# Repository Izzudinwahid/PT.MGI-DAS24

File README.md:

# PT.MGI-DAS24
Rangkaian Digital Alert System 24 Channel 110V

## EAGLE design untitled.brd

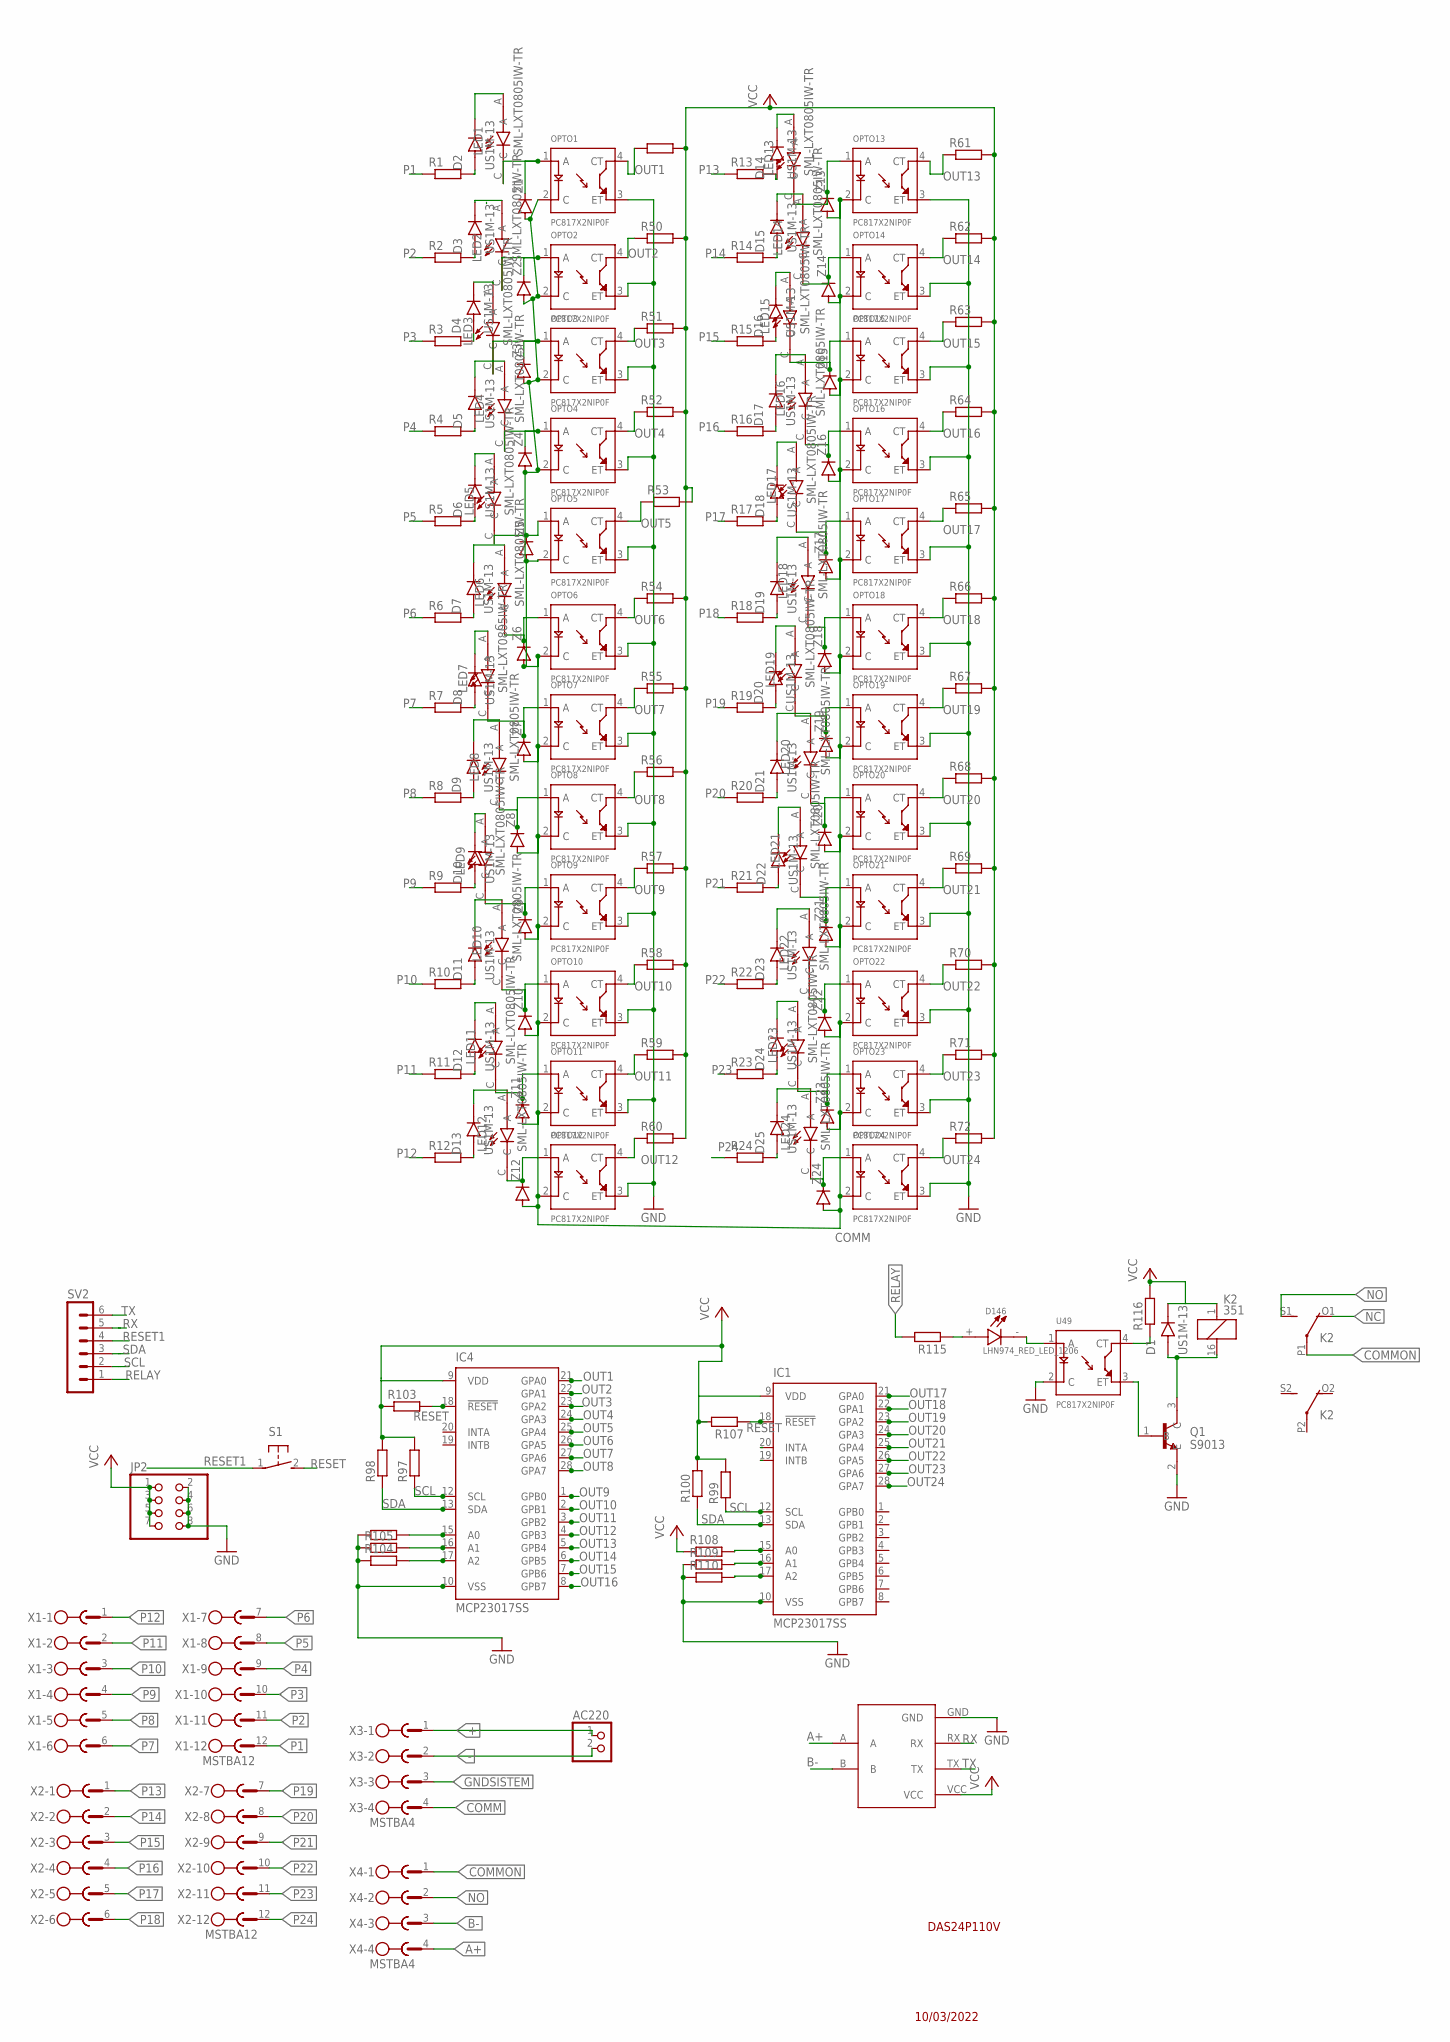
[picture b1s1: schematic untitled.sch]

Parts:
AC220: PINHD-1X2; 1X02
D1, D2, D3, D4, D5, D6, D7, D8, D9, D10, D11, D12, D13, D14, D15, D16, D17, D18, D19, D20, D21, D22, D23, D24, D25: US1M-13; DIOM5226X240N
D146: LHN974_RED_LED_1206; LEDC3216X120N
IC1, IC4: MCP23017SS; SSOP28DB
JP2: PINHD-2X4; 2X04
K2: 351
LED1, LED2, LED3, LED4, LED5, LED6, LED7, LED8, LED9, LED10, LED11, LED12, LED13, LED14, LED15, LED16, LED17, LED18, LED19, LED20, LED21, LED22, LED23, LED24: SML-LXT0805IW-TR; LEDC2012X120N
OPTO1, OPTO2, OPTO3, OPTO4, OPTO5, OPTO6, OPTO7, OPTO8, OPTO9, OPTO10, OPTO11, OPTO12, OPTO13, OPTO14, OPTO15, OPTO16, OPTO17, OPTO18, OPTO19, OPTO20, OPTO21, OPTO22, OPTO23, OPTO24: PC817X2NIP0F; SOT254P975X400-4N
Q1: S9013; SOT95P240X120-3N
R1, R2, R3, R4, R5, R6, R7, R8, R9, R10, R11, R12, R13, R14, R15, R16, R17, R18, R19, R20, R21, R22, R23, R24: R-EU_0414/15; 0414/15
R49, R50, R51, R52, R53, R54, R55, R56, R57, R58, R59, R60, R61, R62, R63, R64, R65, R66, R67, R68, R69, R70, R71, R72, R97, R98, R99, R100, R103, R104, R105, R106, R107, R108, R109, R110, R115, R116: R-EU_R0805; R0805
S1: 31-XX; B3F-31XX
SV2: MA06-1
TTL-RS1: TTL-RS485
U49: PC817X2NIP0F; SOT254P975X400-4N
X1, X2: MSTBA12
X3, X4: MSTBA4
Z1, Z2, Z3, Z4, Z5, Z6, Z7, Z8, Z9, Z10, Z11, Z12, Z13, Z14, Z15, Z16, Z17, Z18, Z19, Z20, Z21, Z22, Z23, Z24: DIODE-SOD123; SOD123

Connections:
+: AC220.1, X3.1; also elsewhere on the board
-: AC220.2, X3.2; also elsewhere on the board
A+: TTL-RS1.A, X4.4; also elsewhere on the board
B-: TTL-RS1.B, X4.3; also elsewhere on the board
COMM: OPTO1.2 (C), OPTO2.2 (C), OPTO3.2 (C), OPTO4.2 (C), OPTO5.2 (C), OPTO6.2 (C), OPTO7.2 (C), OPTO8.2 (C), OPTO9.2 (C), OPTO10.2 (C), OPTO11.2 (C), OPTO12.2 (C), OPTO13.2 (C), OPTO14.2 (C), OPTO15.2 (C), OPTO16.2 (C), OPTO17.2 (C), OPTO18.2 (C), OPTO19.2 (C), OPTO20.2 (C), OPTO21.2 (C), OPTO22.2 (C), OPTO23.2 (C), OPTO24.2 (C), X3.4, Z1.A, Z2.A, Z3.A, Z4.A, Z5.A, Z6.A, Z7.A, Z8.A, Z9.A, Z10.A, Z11.A, Z12.A, Z13.A, Z14.A, Z15.A, Z16.A, Z17.A, Z18.A, Z19.A, Z20.A, Z21.A, Z22.A, Z23.A, Z24.A; also elsewhere on the board
COMMON: K2.P1, X4.1; also elsewhere on the board
GND: IC1.10 (VSS), IC4.10 (VSS), JP2.2, JP2.4, JP2.6, JP2.8, OPTO1.3 (ET), OPTO2.3 (ET), OPTO3.3 (ET), OPTO4.3 (ET), OPTO5.3 (ET), OPTO6.3 (ET), OPTO7.3 (ET), OPTO8.3 (ET), OPTO9.3 (ET), OPTO10.3 (ET), OPTO11.3 (ET), OPTO12.3 (ET), OPTO13.3 (ET), OPTO14.3 (ET), OPTO15.3 (ET), OPTO16.3 (ET), OPTO17.3 (ET), OPTO18.3 (ET), OPTO19.3 (ET), OPTO20.3 (ET), OPTO21.3 (ET), OPTO22.3 (ET), OPTO23.3 (ET), OPTO24.3 (ET), Q1.2 (E), R104.1, R105.1, R106.1, R109.1, R110.1, TTL-RS1.GND, U49.2 (C)
unnamed: D2.A, R1.2
unnamed: LED10.C, OPTO10.1 (A), Z10.C
unnamed: D3.A, R2.2
unnamed: D4.A, R3.2
unnamed: LED1.C, OPTO1.1 (A), Z1.C
unnamed: D5.A, R4.2
unnamed: D2.C (K), LED1.A
unnamed: D6.A, R5.2
unnamed: D3.C (K), LED2.A
unnamed: D7.A, R6.2
unnamed: LED2.C, OPTO2.1 (A), Z2.C
unnamed: D8.A, R7.2
unnamed: D4.C (K), LED3.A
unnamed: D9.A, R8.2
unnamed: LED3.C, OPTO3.1 (A), Z3.C
unnamed: D15.A, R14.2
unnamed: D5.C (K), LED4.A
unnamed: LED4.C, OPTO4.1 (A), Z4.C
unnamed: D10.A, R9.2
unnamed: D6.C (K), LED5.A
unnamed: LED5.C, OPTO5.1 (A), Z5.C
unnamed: D7.C (K), LED6.A
unnamed: D11.A, R10.2
unnamed: D8.C (K), LED7.A
unnamed: LED6.C, OPTO6.1 (A), Z6.C
unnamed: D12.A, R11.2
unnamed: D13.A, R12.2
unnamed: D14.A, R13.2
unnamed: D16.A, R15.2
unnamed: D17.A, R16.2
unnamed: D9.C (K), LED8.A
unnamed: D10.C (K), LED9.A
unnamed: D11.C (K), LED10.A
unnamed: D18.A, R17.2
unnamed: D12.C (K), LED11.A
unnamed: D13.C (K), LED12.A
unnamed: D14.C (K), LED13.A
unnamed: D19.A, R18.2
unnamed: D15.C (K), LED14.A
unnamed: D16.C (K), LED15.A
unnamed: D17.C (K), LED16.A
unnamed: D20.A, R19.2
unnamed: D18.C (K), LED17.A
unnamed: D19.C (K), LED18.A
unnamed: D20.C (K), LED19.A
unnamed: D21.C (K), LED20.A
unnamed: D22.C (K), LED21.A
unnamed: D21.A, R20.2
unnamed: D23.C (K), LED22.A
unnamed: D24.C (K), LED23.A
unnamed: D25.C (K), LED24.A
unnamed: LED7.C, OPTO7.1 (A), Z7.C
unnamed: D22.A, R21.2
unnamed: LED8.C, OPTO8.1 (A), Z8.C
unnamed: LED9.C, OPTO9.1 (A), Z9.C
unnamed: LED11.C, OPTO11.1 (A), Z11.C
unnamed: LED12.C, OPTO12.1 (A), Z12.C
unnamed: D23.A, R22.2
unnamed: LED13.C, OPTO13.1 (A), Z13.C
unnamed: LED14.C, OPTO14.1 (A), Z14.C
unnamed: LED15.C, OPTO15.1 (A), Z15.C
unnamed: D24.A, R23.2
unnamed: LED16.C, OPTO16.1 (A), Z16.C
unnamed: LED17.C, OPTO17.1 (A), Z17.C
unnamed: LED18.C, OPTO18.1 (A), Z18.C
unnamed: D25.A, R24.2
unnamed: LED19.C, OPTO19.1 (A), Z19.C
unnamed: LED20.C, OPTO20.1 (A), Z20.C
unnamed: LED21.C, OPTO21.1 (A), Z21.C
unnamed: LED22.C, OPTO22.1 (A), Z22.C
unnamed: LED23.C, OPTO23.1 (A), Z23.C
unnamed: LED24.C, OPTO24.1 (A), Z24.C
unnamed: D146.-, U49.1 (A)
unnamed: D146.+, R115.1
unnamed: R116.1, U49.4 (CT)
unnamed: D1.A, K2.16 (2), Q1.3 (C)
unnamed: Q1.1 (B), U49.3 (ET)
unnamed: IC1.15 (A0), R108.2
unnamed: IC1.16 (A1), R109.2
unnamed: IC4.15 (A0), R106.2
unnamed: IC4.16 (A1), R105.2
unnamed: IC4.17 (A2), R104.2
unnamed: IC1.17 (A2), R110.2
NC: K2.O1 (O); also elsewhere on the board
NO: K2.S1 (S), X4.2; also elsewhere on the board
OUT1: IC4.21 (GPA0), OPTO1.4 (CT), R49.1
OUT2: IC4.22 (GPA1), OPTO2.4 (CT), R50.1
OUT3: IC4.23 (GPA2), OPTO3.4 (CT), R51.1
OUT4: IC4.24 (GPA3), OPTO4.4 (CT), R52.1
OUT5: IC4.25 (GPA4), OPTO5.4 (CT), R53.1
OUT6: IC4.26 (GPA5), OPTO6.4 (CT), R54.1
OUT7: IC4.27 (GPA6), OPTO7.4 (CT), R55.1
OUT8: IC4.28 (GPA7), OPTO8.4 (CT), R56.1
OUT9: IC4.1 (GPB0), OPTO9.4 (CT), R57.1
OUT10: IC4.2 (GPB1), OPTO10.4 (CT), R58.1
OUT11: IC4.3 (GPB2), OPTO11.4 (CT), R59.1
OUT12: IC4.4 (GPB3), OPTO12.4 (CT), R60.1
OUT13: IC4.5 (GPB4), OPTO13.4 (CT), R61.1
OUT14: IC4.6 (GPB5), OPTO14.4 (CT), R62.1
OUT15: IC4.7 (GPB6), OPTO15.4 (CT), R63.1
OUT16: IC4.8 (GPB7), OPTO16.4 (CT), R64.1
OUT17: IC1.21 (GPA0), OPTO17.4 (CT), R65.1
OUT18: IC1.22 (GPA1), OPTO18.4 (CT), R66.1
OUT19: IC1.23 (GPA2), OPTO19.4 (CT), R67.1
OUT20: IC1.24 (GPA3), OPTO20.4 (CT), R68.1
OUT21: IC1.25 (GPA4), OPTO21.4 (CT), R69.1
OUT22: IC1.26 (GPA5), OPTO22.4 (CT), R70.1
OUT23: IC1.27 (GPA6), OPTO23.4 (CT), R71.1
OUT24: IC1.28 (GPA7), OPTO24.4 (CT), R72.1
P1: R1.1, X1.12
P2: R2.1, X1.11
P3: R3.1, X1.10
P4: R4.1, X1.9
P5: R5.1, X1.8
P6: R6.1, X1.7
P7: R7.1, X1.6
P8: R8.1, X1.5
P9: R9.1, X1.4
P10: R10.1, X1.3
P11: R11.1, X1.2
P12: R12.1, X1.1
P13: R13.1, X2.1
P14: R14.1, X2.2
P15: R15.1, X2.3
P16: R16.1, X2.4
P17: R17.1, X2.5
P18: R18.1, X2.6
P19: R19.1, X2.7
P20: R20.1, X2.8
P21: R21.1, X2.9
P22: R22.1, X2.10
P23: R23.1, X2.11
P24: R24.1, X2.12
RELAY: R115.2, SV2.1
RESET: IC1.18 (!RESET), IC4.18 (!RESET), R103.2, R107.1, S1.2 (S)
RESET1: S1.1, SV2.4
RX: SV2.5, TTL-RS1.RX
SCL: IC1.12 (SCL), IC4.12 (SCL), R97.1, R99.1, SV2.2
SDA: IC1.13 (SDA), IC4.13 (SDA), R98.1, R100.1, SV2.3
TX: SV2.6, TTL-RS1.TX
VCC: D1.C (K), IC1.9 (VDD), IC4.9 (VDD), JP2.1, JP2.3, JP2.5, JP2.7, K2.1, R49.2, R50.2, R51.2, R52.2, R53.2, R54.2, R55.2, R56.2, R57.2, R58.2, R59.2, R60.2, R61.2, R62.2, R63.2, R64.2, R65.2, R66.2, R67.2, R68.2, R69.2, R70.2, R71.2, R72.2, R97.2, R98.2, R99.2, R100.2, R103.1, R107.2, R108.1, R116.2, TTL-RS1.VCC

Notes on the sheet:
DAS24P110V
10/03/2022

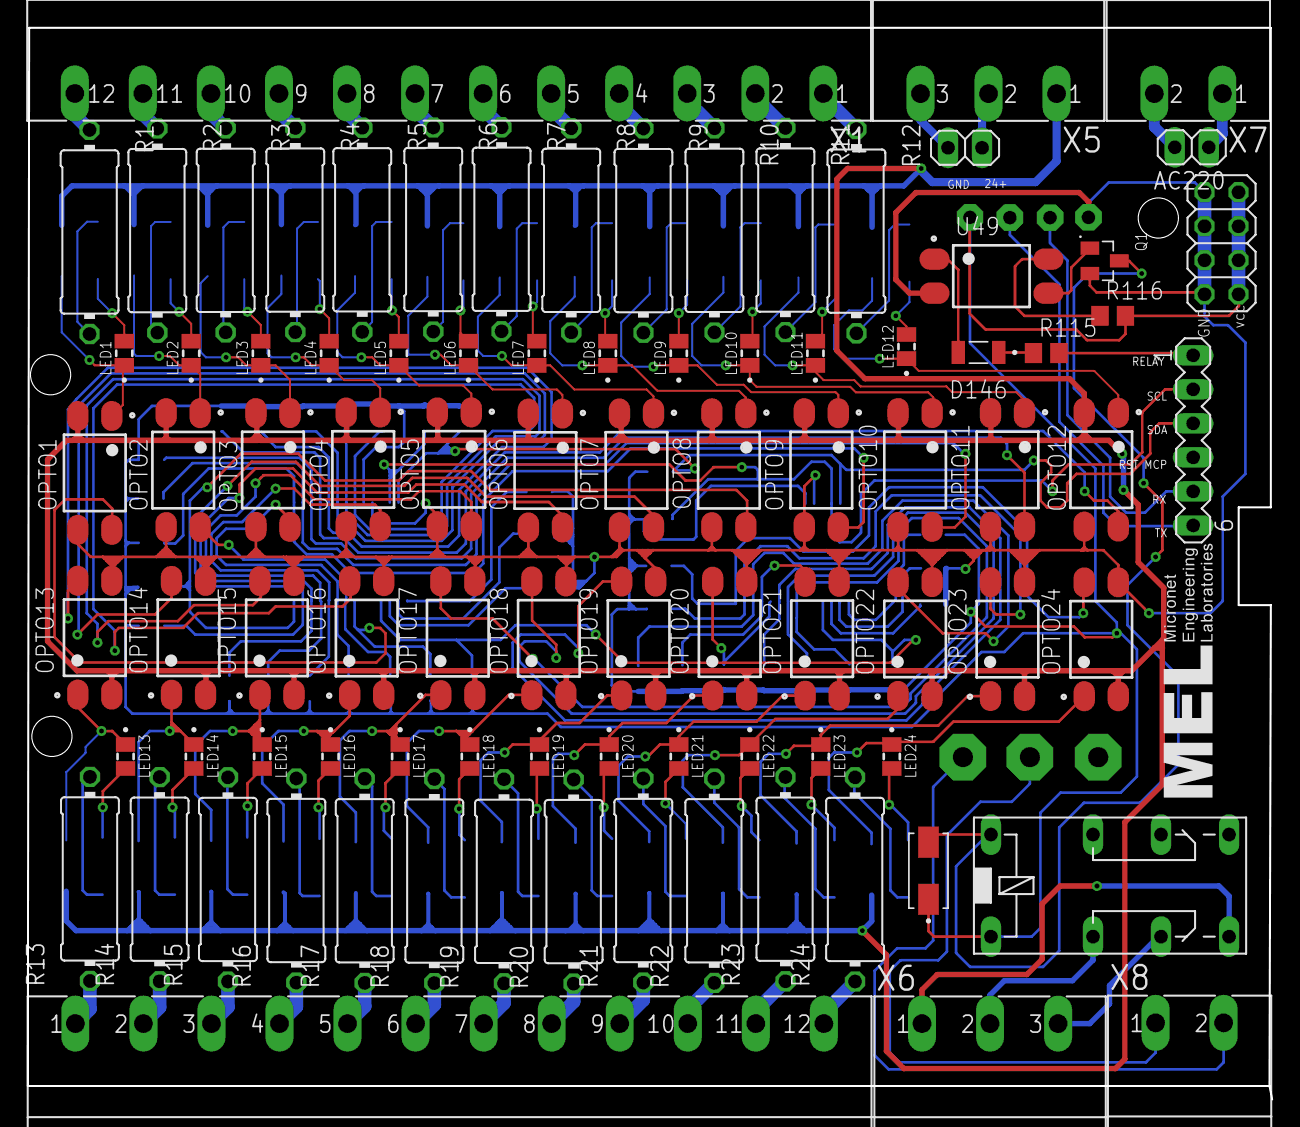
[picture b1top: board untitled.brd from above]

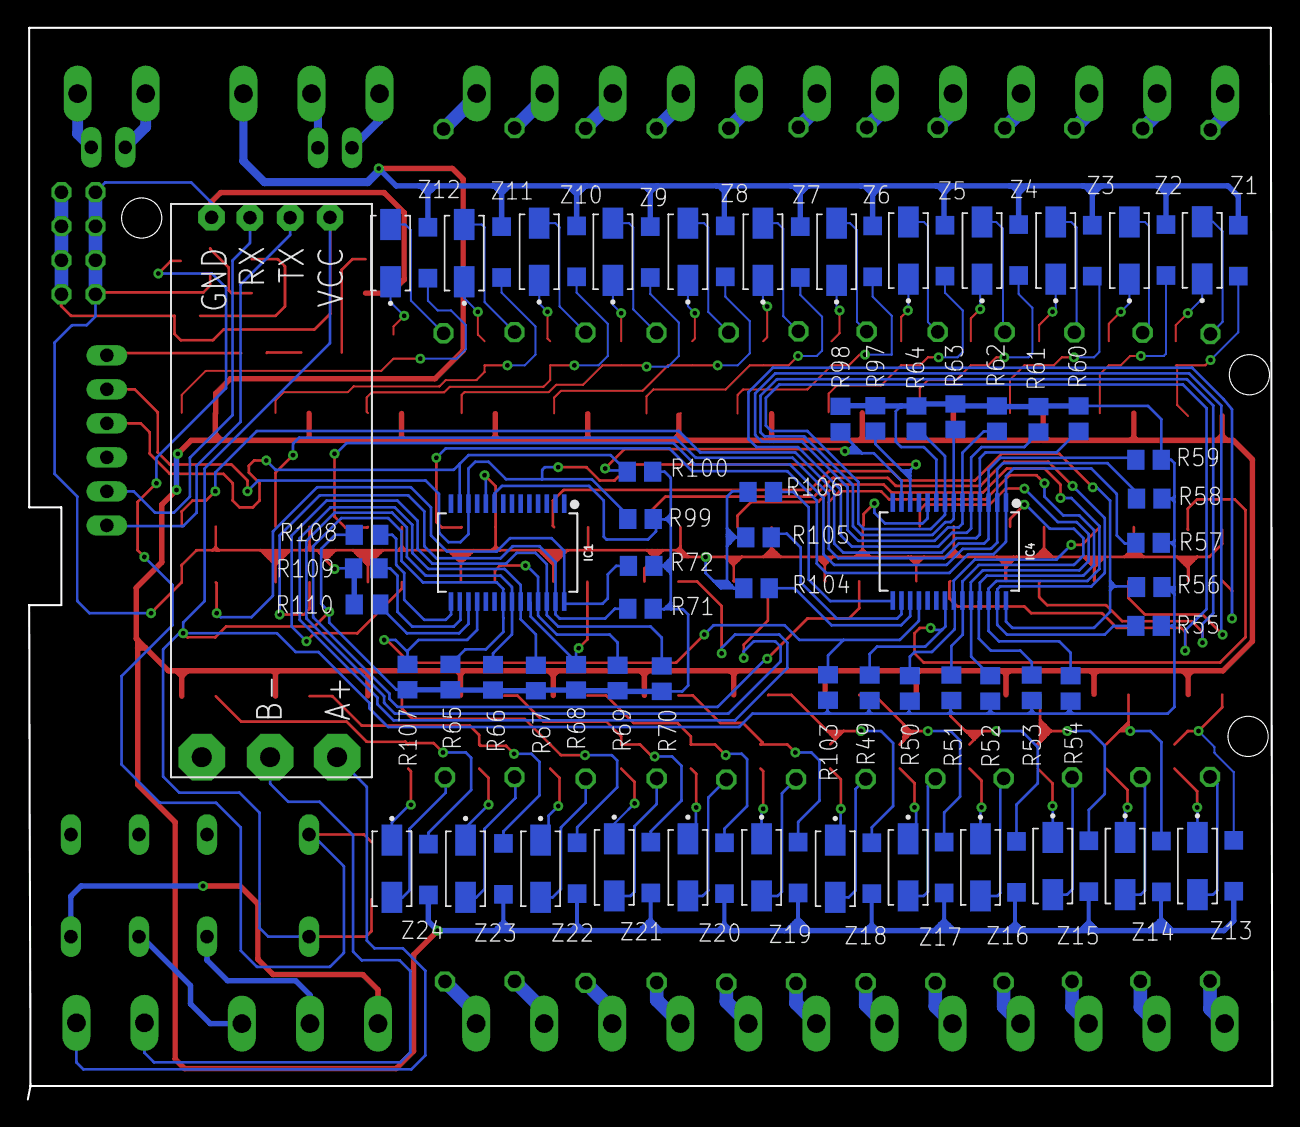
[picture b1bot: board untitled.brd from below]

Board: 2 copper layers, 92.9 x 80.0 mm, 176 parts (87 on the bottom side), 149 nets.

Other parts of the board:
AC1: 1X02
X5, X6: MSTBA3
X7, X8: MSTBA2

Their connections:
24V+: AC1.2, X5.2
24V-: AC1.1, X5.3
+: X7.1; also elsewhere on the board
-: X7.2; also elsewhere on the board
A+: X8.2; also elsewhere on the board
B-: X8.1; also elsewhere on the board
COMM: X5.1; also elsewhere on the board
COMMON: X6.2; also elsewhere on the board
NC: X6.3; also elsewhere on the board
NO: X6.1; also elsewhere on the board

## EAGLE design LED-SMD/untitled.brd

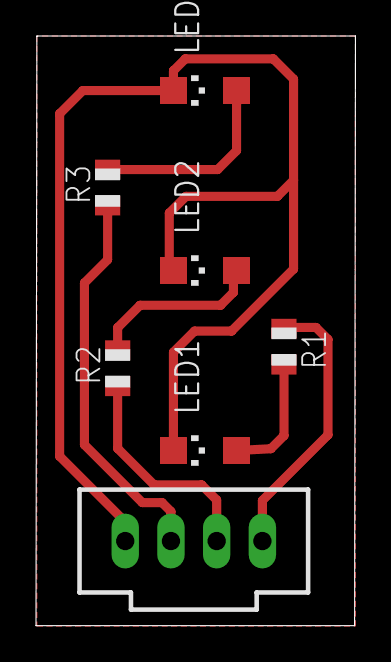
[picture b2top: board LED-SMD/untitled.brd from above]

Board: 2 copper layers, 17.7 x 32.8 mm, 7 parts (0 on the bottom side), 7 nets.

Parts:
LED1, LED2, LED3: CHIPLED_1206
R1, R2, R3: R0805
X1: C-GRID-04-70543; 70543-04

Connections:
unnamed: R1.1, X1.4
unnamed: R2.1, X1.3
unnamed: R3.1, X1.2
unnamed: LED1.A, R1.2
unnamed: LED2.A, R2.2
unnamed: LED3.A, R3.2
unnamed: LED1.C, LED2.C, LED3.C, X1.1

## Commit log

2022-08-10 menambahkan File .sch dan .brd
2022-08-12 revisi jalur
2022-08-12 revisi board
2022-08-12 revisi .brd
2022-09-21 menambahkan lampu
2023-05-12 membuat PCB led smd
